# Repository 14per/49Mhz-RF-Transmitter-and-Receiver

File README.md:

# 49Mhz-RF-Transmitter-and-Receiver
Transmitter and Receiver Operating at 49.152Mhz 

<!-- 

-->

<!--

-->

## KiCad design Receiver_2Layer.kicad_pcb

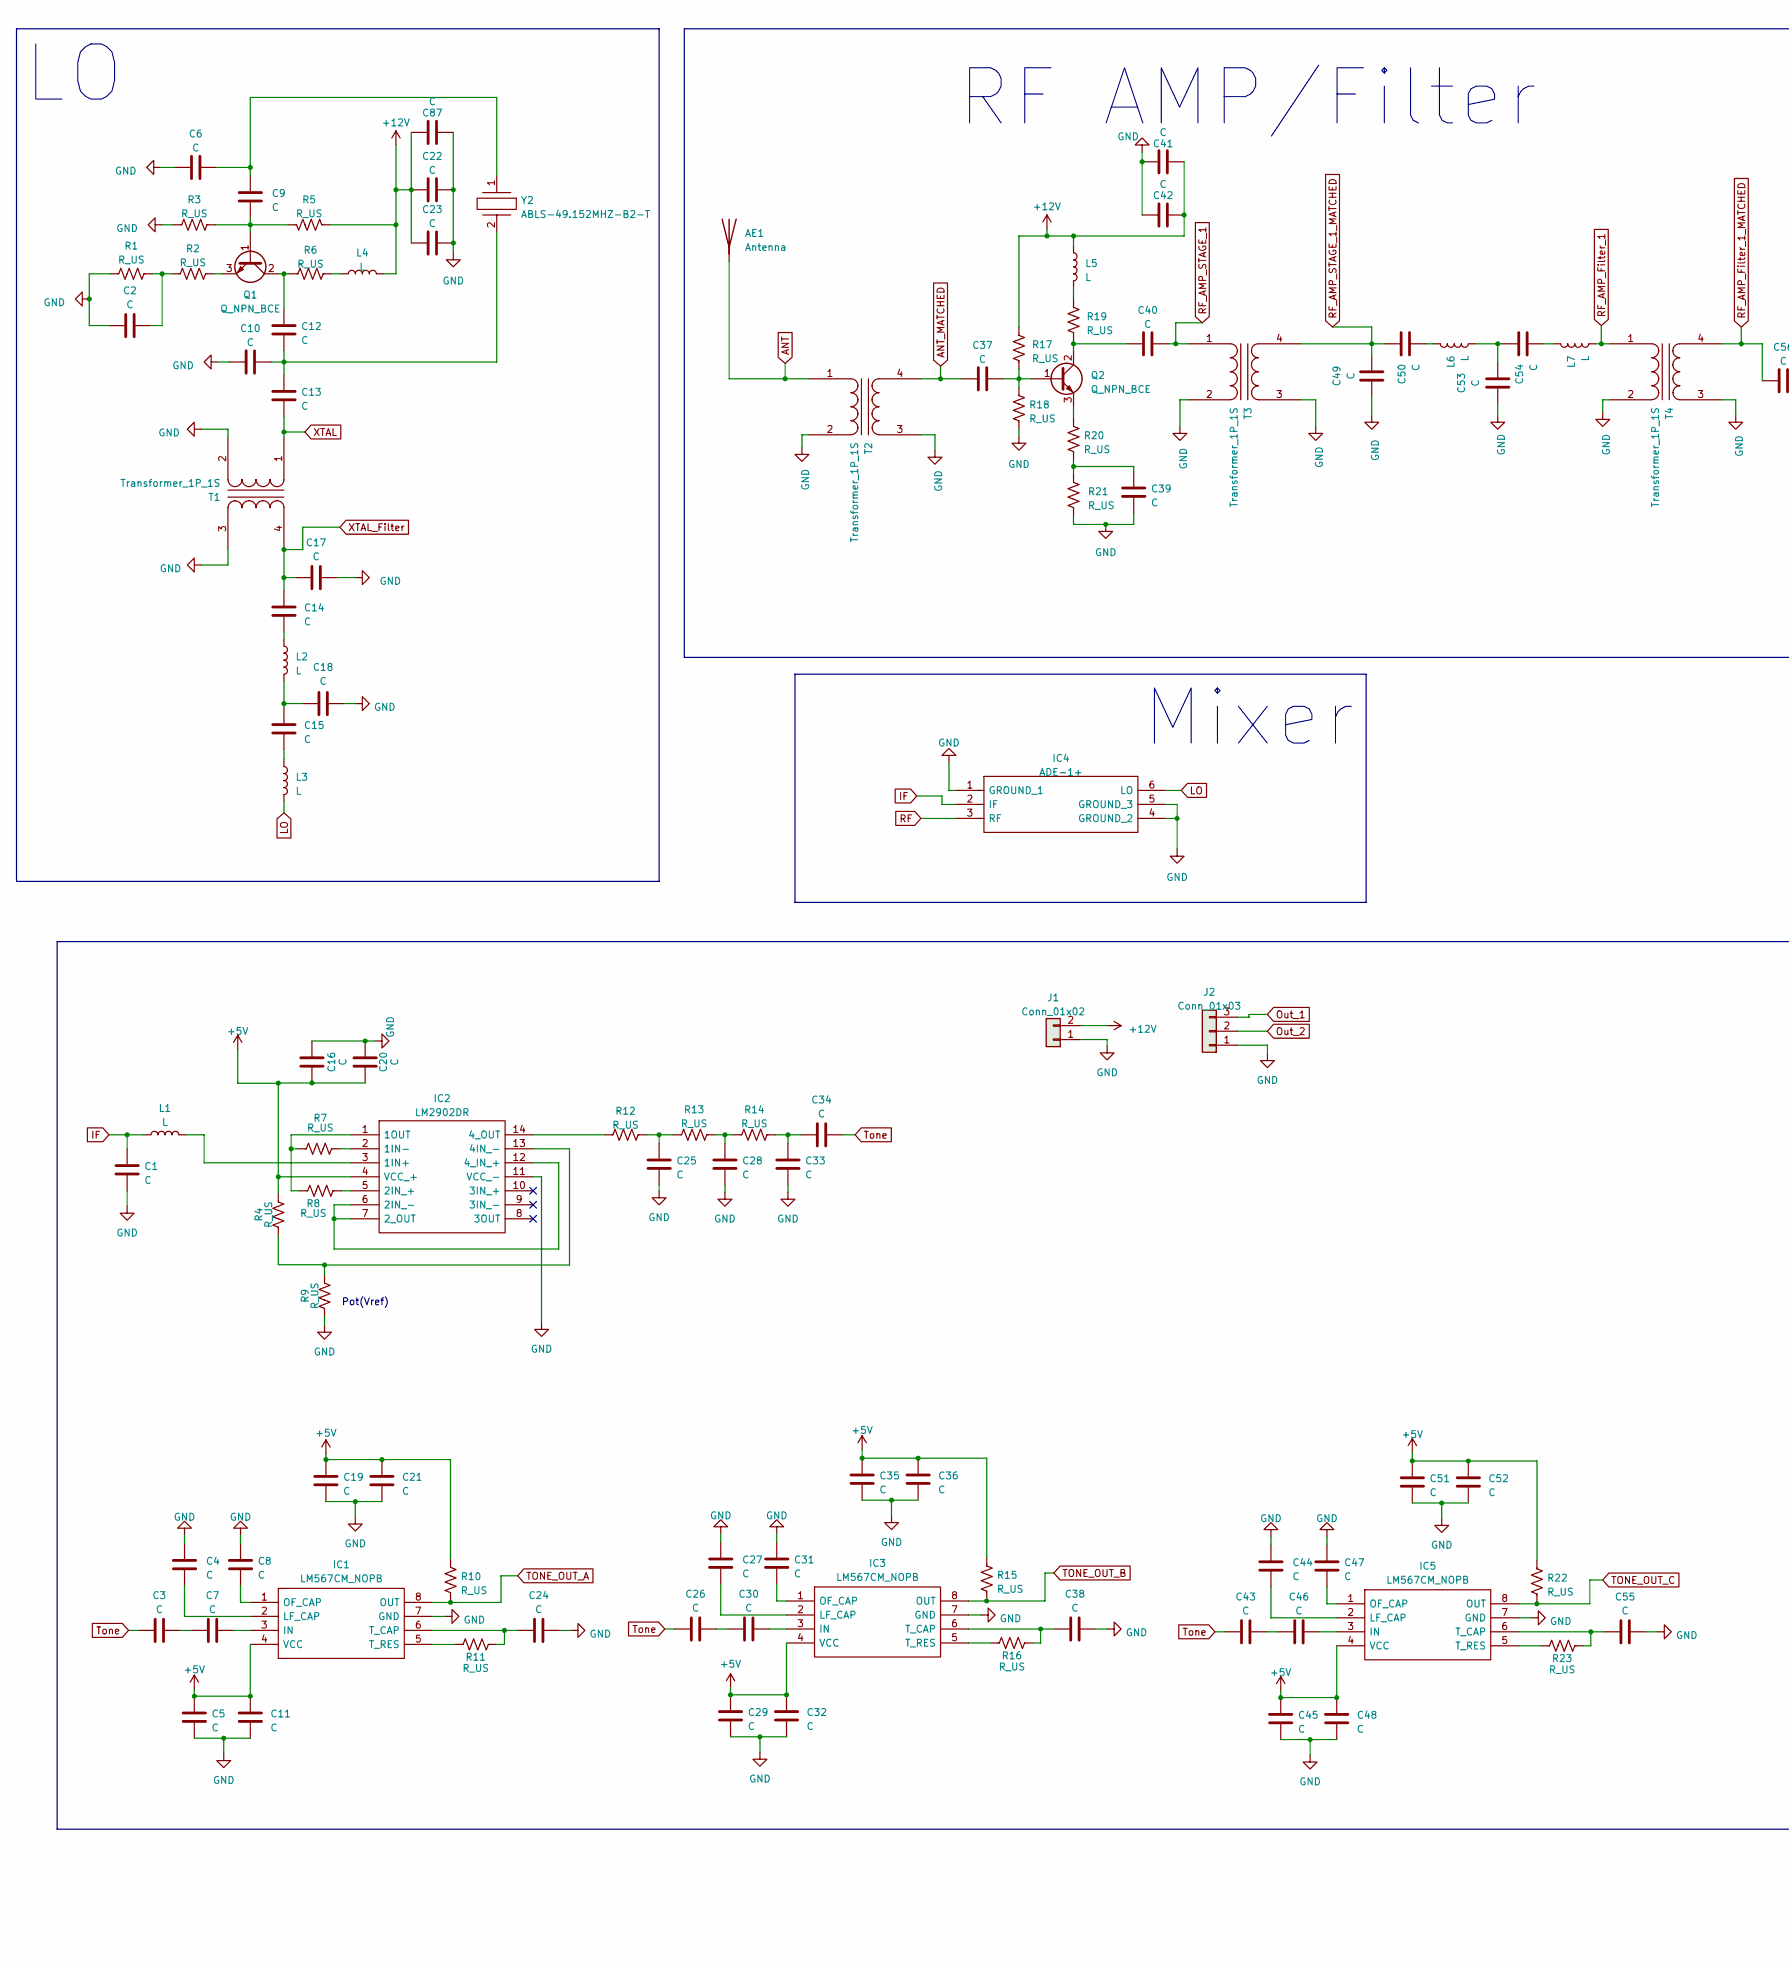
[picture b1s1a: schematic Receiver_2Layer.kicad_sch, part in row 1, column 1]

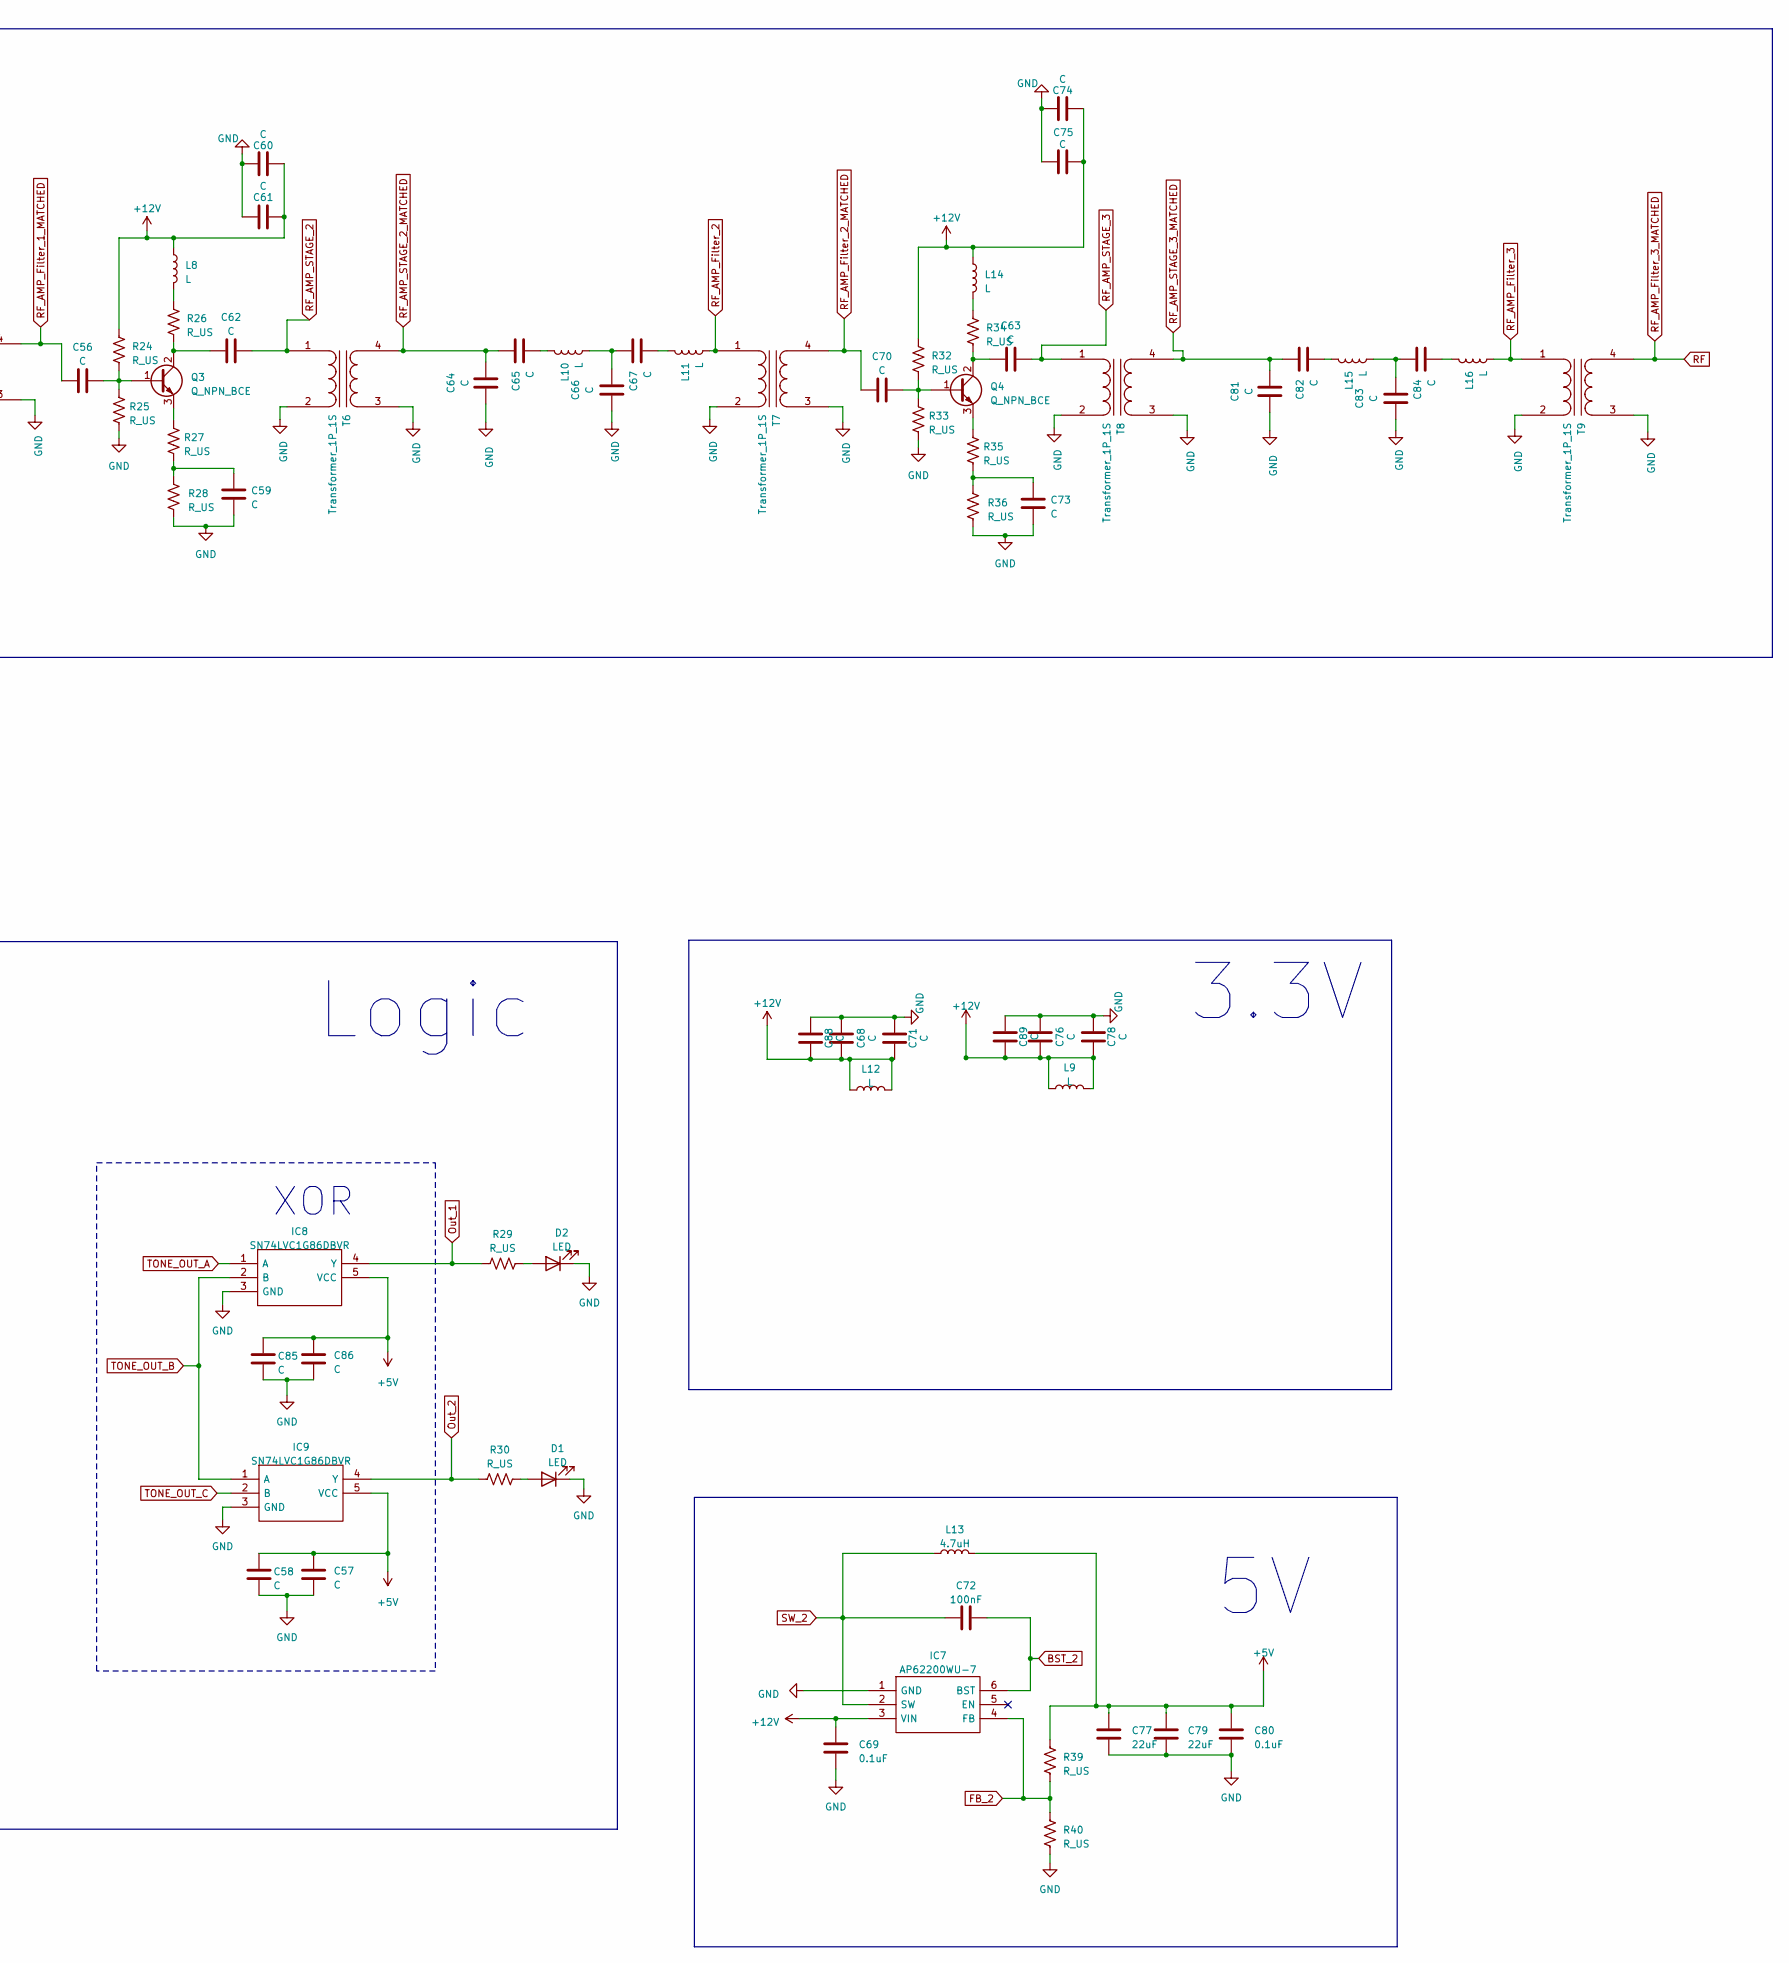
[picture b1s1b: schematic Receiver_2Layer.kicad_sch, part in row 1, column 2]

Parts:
AE1: Antenna
C1, C2, C3, C4, C5, C6, C7, C8, C9, C10, C11, C12, C13, C14, C15, C16, C17, C18, C19, C20, C21, C22, C23, C24, C25, C26, C27, C28, C29, C30, C31, C32, C33, C34, C35, C36, C37, C38, C39, C40, C41, C42, C43, C44, C45, C46, C47, C48, C49, C50, C51, C52, C53, C54, C55, C56, C57, C58, C59, C60, C61, C62, C63, C64, C65, C66, C67, C68, C70, C71, C73, C74, C75, C76, C78, C81, C82, C83, C84, C85, C86, C87, C88, C89: C
C69, C80: 0.1uF
C72: 100nF
C77, C79: 22uF
D1, D2: LED
IC1, IC3, IC5: LM567CM_NOPB; Mouser Part Number 926-LM567CM/NOPB
IC2: LM2902DR; Mouser Part Number 595-LM2902DR
IC4: ADE-1+; Mouser Part Number 139-ADE-1
IC7: AP62200WU-7; Manufacturer_Part_Number AP62200WU-7; Mouser Part Number 621-AP62200WU-7
IC8, IC9: SN74LVC1G86DBVR; Mouser Part Number 595-SN74LVC1G86DBVR
J1: Conn_01x02
J2: Conn_01x03
L1, L2, L3, L4, L5, L6, L7, L8, L9, L10, L11, L12, L14, L15, L16: L
L13: 4.7uH
Q1, Q2, Q3, Q4: Q_NPN_BCE
R1, R2, R3, R4, R5, R6, R7, R8, R9, R10, R11, R12, R13, R14, R15, R16, R17, R18, R19, R20, R21, R22, R23, R24, R25, R26, R27, R28, R29, R30, R32, R33, R34, R35, R36, R39, R40: R_US
T1, T2, T3, T4, T6, T7, T8, T9: Transformer_1P_1S; Transformer_THT_14mm
Y2: ABLS-49.152MHZ-B2-T; Mouser Part Number 815-ABLS-49.152-B2

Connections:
+5V: C5.2, C11.2, C16.1, C19.2, C20.1, C21.2, C29.2, C32.2, C35.2, C36.2, C45.2, C48.2, C51.2, C52.2, C57.2, C58.2, C77.1, C79.1, C80.2, C85.2, C86.2, IC1.4 (VCC), IC2.4 (VCC_+), IC3.4 (VCC), IC5.4 (VCC), IC8.5 (VCC), IC9.5 (VCC), L13.2, R4.2, R10.2, R15.2, R22.2, R39.1
ANT: AE1.1 (A), T2.1 (AA)
ANT_MATCHED: C37.1, T2.4 (SB)
BST_2: C72.2, IC7.6 (BST)
FB_2: IC7.4 (FB), R39.2, R40.1
IF: C1.1, IC4.2 (IF), L1.1
LO: IC4.6 (LO), L3.2
unnamed: C2.2, R1.2, R2.1
unnamed: C3.2, C7.1
unnamed: C6.1, C9.2, Y2.1
unnamed: C10.2, C12.2, C13.1, Y2.2
unnamed: C14.1, L2.1
unnamed: C15.1, L3.1
unnamed: C15.2, C18.1, L2.2
unnamed: C25.1, R12.2, R13.1
unnamed: C26.2, C30.1
unnamed: C28.1, R13.2, R14.1
unnamed: C33.1, C34.1, R14.2
unnamed: C39.1, R20.1, R21.2
unnamed: C43.2, C46.1
unnamed: C50.1, L6.1
unnamed: C53.1, C54.2, L6.2
unnamed: C54.1, L7.1
unnamed: C59.1, R27.1, R28.2
unnamed: C65.1, L10.1
unnamed: C66.1, C67.2, L10.2
unnamed: C67.1, L11.1
unnamed: C73.1, R35.1, R36.2
unnamed: C82.1, L15.1
unnamed: C83.1, C84.2, L15.2
unnamed: C84.1, L16.1
unnamed: D1.2 (A), R30.2
unnamed: D2.2 (A), R29.2
unnamed: C7.2, IC1.3 (IN)
unnamed: C4.1, IC1.2 (LF_CAP)
unnamed: C8.1, IC1.1 (OF_CAP)
unnamed: C24.1, IC1.6 (T_CAP), R11.1
unnamed: IC1.5 (T_RES), R11.2
unnamed: IC2.3 (1IN+), L1.2
unnamed: IC2.2 (1IN-), R7.2
unnamed: IC2.1 (1OUT), R7.1, R8.1
unnamed: IC2.5 (2IN_+), R8.2
unnamed: IC2.6 (2IN_-), IC2.7 (2_OUT), IC2.12 (4_IN_+)
unnamed: IC2.13 (4IN_-), R4.1, R9.2
unnamed: IC2.14 (4_OUT), R12.1
unnamed: C30.2, IC3.3 (IN)
unnamed: C27.1, IC3.2 (LF_CAP)
unnamed: C31.1, IC3.1 (OF_CAP)
unnamed: C38.1, IC3.6 (T_CAP), R16.1
unnamed: IC3.5 (T_RES), R16.2
unnamed: C46.2, IC5.3 (IN)
unnamed: C44.1, IC5.2 (LF_CAP)
unnamed: C47.1, IC5.1 (OF_CAP)
unnamed: C55.1, IC5.6 (T_CAP), R23.1
unnamed: IC5.5 (T_RES), R23.2
unnamed: L4.1, R6.2
unnamed: L5.2, R19.2
unnamed: L8.2, R26.2
unnamed: L14.2, R34.2
unnamed: C9.1, Q1.1 (B), R3.2, R5.2
unnamed: C12.1, Q1.2 (C), R6.1
unnamed: Q1.3 (E), R2.2
unnamed: C37.2, Q2.1 (B), R17.1, R18.2
unnamed: C40.1, Q2.2 (C), R19.1
unnamed: Q2.3 (E), R20.2
unnamed: C56.2, Q3.1 (B), R24.1, R25.2
unnamed: C62.1, Q3.2 (C), R26.1
unnamed: Q3.3 (E), R27.2
unnamed: C70.2, Q4.1 (B), R32.1, R33.2
unnamed: C63.1, Q4.2 (C), R34.1
unnamed: Q4.3 (E), R35.2
Out_1: IC8.4 (Y), J2.3, R29.1
Out_2: IC9.4 (Y), J2.2, R30.1
RF: IC4.3 (RF), T9.4 (SB)
RF_AMP_Filter_1: L7.2, T4.1 (AA)
RF_AMP_Filter_1_MATCHED: C56.1, T4.4 (SB)
RF_AMP_Filter_2: L11.2, T7.1 (AA)
RF_AMP_Filter_2_MATCHED: C70.1, T7.4 (SB)
RF_AMP_Filter_3: L16.2, T9.1 (AA)
RF_AMP_STAGE_1: C40.2, T3.1 (AA)
RF_AMP_STAGE_1_MATCHED: C49.1, C50.2, T3.4 (SB)
RF_AMP_STAGE_2: C62.2, T6.1 (AA)
RF_AMP_STAGE_2_MATCHED: C64.1, C65.2, T6.4 (SB)
RF_AMP_STAGE_3: C63.2, T8.1 (AA)
RF_AMP_STAGE_3_MATCHED: C81.1, C82.2, T8.4 (SB)
SW_2: C72.1, IC7.2 (SW), L13.1
TONE_OUT_A: IC1.8 (OUT), IC8.1 (A), R10.1
TONE_OUT_B: IC3.8 (OUT), IC8.2 (B), IC9.1 (A), R15.1
TONE_OUT_C: IC5.8 (OUT), IC9.2 (B), R22.1
Tone: C3.1, C26.1, C34.2, C43.1
XTAL: C13.2, T1.1 (AA)
XTAL_Filter: C14.2, C17.1, T1.4 (SB)

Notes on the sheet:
Mixer
RF AMP/Filter
Logic
Pot(Vref)
XOR
3.3V

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
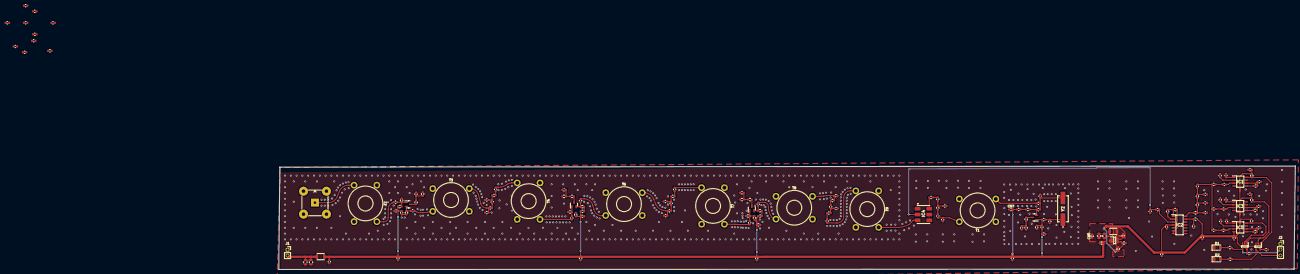
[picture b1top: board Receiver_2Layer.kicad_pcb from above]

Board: 2 copper layers, 445.5 x 45.3 mm, 164 parts (0 on the bottom side), 94 nets.
